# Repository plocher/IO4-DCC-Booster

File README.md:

# IO4-DCC-Booster
## License: CERN Open Hardware Licence v1.2

IO4 DCC Booster

A DIY DCC booster for a BOM cost of about $20 when using bulk China/eBay parts.

I was working on designing a motor shield using the $10 IBT-2
H-Bridge when I came across the work done by D. Bodnar at
[train electronics.com](http://www.trainelectronics.com/DCC_Arduino/DCC_Booster/)

I wanted to use one of these for every control point on my layout
instead of a DCC circuit breaker + booster power district mashup.
As the DCC Breakers are at least double the DIY cost for these
dedicated boosters, and I will end up with 10-20 control points on
my SPCoast layout, the savings might actually cover the development
costs :-)

These boosters DO NOT support auto-reverse, and the sketch software
doesn't try to do soft start detection of sound decoder capacitor
inrush currents.  Since there will be on average a single train
powered by each of these boosters on my N-Scale layout, I don't
expect this to be a real issue.  In practice, a simple 1 or 2 amp
unit would probably be good enough; at 5 to 6 amps, this is overkill.

From the original web writeup at trainelectronics.com:

<blockquote>
Introduction

In addition to experimenting with DCC++ over the last few months I
have been trying out different H-Bridges to see if there is one
that would work with DCC++ while delivering more than the 1 to 2
amps that the standard Arduino Motor Shield provides.  Such a option
would a good option for G scale layouts that typically draw much
more power than smaller scales.

I came across a few higher power shields
[that are described here](http://trainelectronics.com/DCC_Arduino/DCC++/)
including one that has an advertised power capability of 43 amps.
While I am a bit skeptical about this claim my tests show that it
has no problem delivering 5 or more amps, more than enough for my
purposes.  I describe how this can be interfaced to the DCC++
controller in the link above.

In order to make the use of this H-Bridge more convenient I decided
to design a stand-alone DCC booster that would attach to a DCC
signal and boost it before powering a track.  The booster is designed
to work with DCC++, Digitrax and other systems.

Hardware - H-Bridge

The H-Bridge is available from eBay, Amazon and other vendors -
just search for "H-Bridge 43 amp BTS7960B".  Make sure you get the
unit that has two BTS7960B devices on it - each is 1/2 of an H-Bridge.
The control signals go to the 8 pins on the front and the power in
and power out wires go to the 4 pin screw terminal connector at the
rear.

This H-Bridge and similar units do not operate on the single PWM
signal that most DCC systems provide.  It needs a right hand rotating
PWM and a left hand PWM.  To change the single PWM signal to two a
simple one transistor circuit is needed.  That circuit can be seen
in the lower left corner of the schematic (below).

The H-Bridge can act as a DCC booster without much more than the
Opto Coupler circuit and the one transistor converter.  The H-Bridge
does hove an over current shutdown capability but it doesn't react
until well over 30 amps are being drawn, way more than we are going
to use.  To get around this problem so that the system shuts down
immediately if the track is shorted an Arduino Pro Mini has been
added.  The Arduino monitors the current sensing pin on the H-Bridge
and can turn it off should it detect a high reading.

</blockquote>

His prototype reused a board he had on hand; this project simply
turns his schematic into a purpose-built board - and adds remote control
(enable/disable and monitoring) via an IO-4 RJ12/6 interface.

The differences:
  * powered by (3.0) the IO-4 Jack / IOexpander and (3.1) by the DC booster power.
  * local control - a maintainer "disable track power" switch
  * remote control
    * enable/disable track power
  * remote feedback
    * enabled
    * occupied
    * overload
  * Loconet and NCE Booster Bus daisy chain command station cable jacks

=== Estimated BOM costs ===
:	$ 1.00  PCB 
:	$10.00  IBT-2 
:	$ 3.50  Pro Mini Clone
:	$ 0.45  6n137
:	$ 0.20  2200uF x2
:	$ 3.00  RJ and Phoenix connectors
:	$ 1.00  SPDT Switch
:	$ 1.00  R/C/LEDs
:	------
:      ~$20.00

The booster will also need a 12-18v 6A+ DC power supply; the logic and
feedback electronics are isolated from the power supply (using opto
isolator for the booster bus and a full wave bridge for the power
supply), so there should be no problems driving a set of boosters
from a single large amperage switching supply.

As with ALL high power systems, use a SLOW BLOW or POLYFUSE in your
power supply feed.  20v at 6A is 120W - similar to a very bright
and hot incandescent bulb, if you remember them.  You don't want
to arc weld or start a fire on your layout if something goes wrong!

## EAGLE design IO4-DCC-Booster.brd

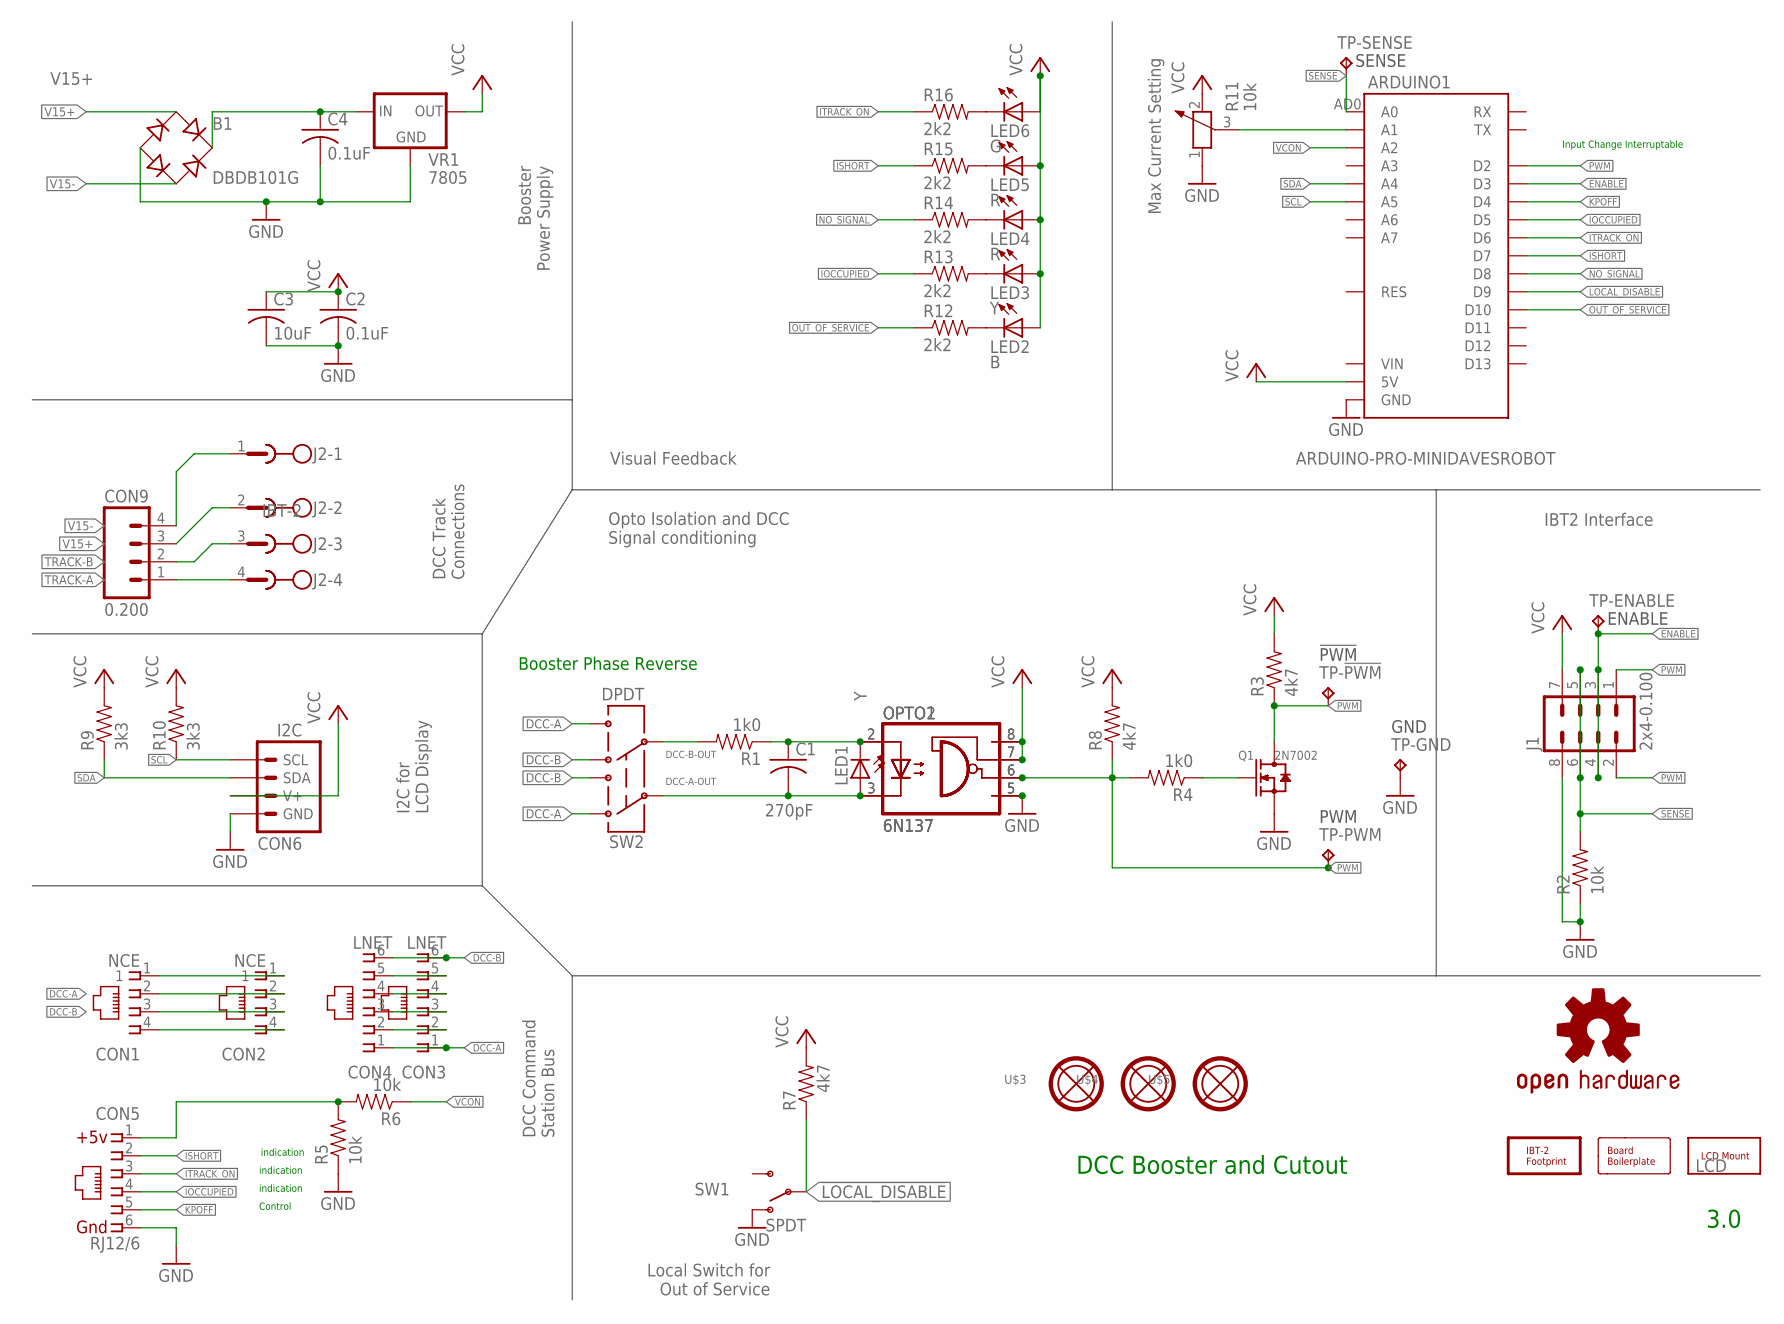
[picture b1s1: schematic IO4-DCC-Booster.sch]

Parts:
ARDUINO1: ARDUINO-PRO-MINIDAVESROBOT; ARDUINO_PRO_MINI_DAVEK
B1: DBDB101G; DB
BOARD1: BOARD100X100-NOHOLES; BOARD-SEEED10X10-NOHOLES
C1: 270pF; 0805-CAP
C2, C4: 0.1uF; 0805-CAP
C3: 10uF; 0805-CAP
CON1, CON2: NCE; 555980-1
CON3, CON4: LNET; RJ25-PANEL
CON5: RJ12/6; RJ25-PANEL
CON6: I2C; I2C-L
CON9: 0.200; MSTBA4
J1: 2x4-0.100; MA04-2
J2: IBT-2; MSTBA4
LCD: LCD; LCD-16X2-SILK
LED1, LED3: Y; 0603-LED
LED2: B; 0603-LED
LED4, LED5: R; 0603-LED
LED6: G; 0603-LED
LOGO1: DOC-OSHW-LOGO-L; OSHW-LOGO-L
OPTO1: 6N137; DIL08
OPTO2: 6N137; SM8
Q1: 2N7002; SOT23
R1, R4: 1k0; 0805-RES
R2, R5, R6: 10k; 0805-RES
R3, R7, R8: 4k7; 0805-RES
R9, R10: 3k3; 0805-RES
R11: 10k; B25X
R12, R13, R14, R15, R16: 2k2; 0805-RES
SW1: SPDT; SWITCH-SPDT-508
SW2: DPDT; 8X8-SQ-PB
TP-!PWM: TPPAD1-13; P1-13
TP-ENABLE: TPPAD1-13; P1-13
TP-GND: TPPAD1-13; P1-13
TP-PWM: TPPAD1-13; P1-13
TP-SENSE: TPPAD1-13; P1-13
U$2: IBT-2
U$3, U$4, U$5: MOUNTINGHOLE
VR1: 7805; TO-252

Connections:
!IOCCUPIED: ARDUINO1.D5, CON5.4, R13.1
!ISHORT: ARDUINO1.D7, CON5.2, R15.1
!ITRACK_ON: ARDUINO1.D6, CON5.3, R16.1
!KPOFF: ARDUINO1.D4, CON5.5
!LOCAL_DISABLE: ARDUINO1.D9, R7.1, SW1.2
!NO_SIGNAL: ARDUINO1.D8, R14.1
!OUT_OF_SERVICE: ARDUINO1.D10, R12.1
!PWM: J1.2, Q1.3 (D), R3.1, TP-!PWM.TP
DCC-A: CON1.2, CON2.2, CON3.1, CON4.1, SW2.1A, SW2.2B
DCC-A-OUT: C1.2, LED1.A, OPTO1.3 (C), OPTO2.3 (C), SW2.1C
DCC-B: CON1.3, CON2.3, CON3.6, CON4.6, SW2.1B, SW2.2A
DCC-B-LIMITED: C1.1, LED1.C, OPTO1.2 (A), OPTO2.2 (A), R1.1
DCC-B-OUT: R1.2, SW2.2C
ENABLE: ARDUINO1.D3, J1.3, J1.4, TP-ENABLE.TP
GND: ARDUINO1.GND@1 (GND), ARDUINO1.GND@2 (GND), ARDUINO1.GND@4 (GND), B1.-, C2.2, C3.2, C4.2, CON5.6, CON6.GND, CON6.GND@1 (GND), J1.8, OPTO1.5 (GND), OPTO2.5 (GND), Q1.2 (S), R2.1, R5.1, R11.1, SW1.1 (O), TP-GND.TP, VR1.2 (GND)
LIMIT: ARDUINO1.AD1 (A1), R11.3 (2)
unnamed: Q1.1 (G), R4.1
unnamed: CON1.4, CON2.4
unnamed: CON1.1, CON2.1
unnamed: CON3.5, CON4.5
unnamed: CON3.4, CON4.4
unnamed: LED4.C, R14.2
unnamed: CON3.3, CON4.3
unnamed: LED2.C, R12.2
unnamed: LED3.C, R13.2
unnamed: LED6.C, R16.2
unnamed: LED5.C, R15.2
unnamed: CON3.2, CON4.2
unnamed: B1.+, C4.1, VR1.1 (IN)
PWM: ARDUINO1.D2, J1.1, OPTO1.6 (VO), OPTO2.6 (VO), R4.2, R8.1, TP-PWM.TP
SCL: ARDUINO1.AD5 (A5), CON6.SCL, CON6.SCL@1 (SCL), R10.1
SDA: ARDUINO1.AD4 (A4), CON6.SDA, CON6.SDA@1 (SDA), R9.1
SENSE: ARDUINO1.AD0 (A0), J1.5, J1.6, R2.2, TP-SENSE.TP
TRACK-A: CON9.1, J2.4
TRACK-B: CON9.2, J2.3
V15+: B1.AC1, CON9.3, J2.2
V15-: B1.AC2, CON9.4, J2.1
VCC: ARDUINO1.5V, C2.1, C3.1, CON6.V+, CON6.V+@1 (V+), J1.7, LED2.A, LED3.A, LED4.A, LED5.A, LED6.A, OPTO1.7 (VE), OPTO1.8 (VCC), OPTO2.7 (VE), OPTO2.8 (VCC), R3.2, R7.2, R8.2, R9.2, R10.2, R11.2 (3), VR1.3 (OUT)
VCOMPUTER: CON5.1, R5.2, R6.2
VCON: ARDUINO1.AD2 (A2), R6.1

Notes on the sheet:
3.0
DCC Booster and Cutout
Control
indication
Input Change Interruptable
Max Current Setting
Visual Feedback
Booster Power Supply
DCC Track Connections
I2C for LCD Display
DCC Command Station Bus
Local Switch for Out of Service
Opto Isolation and DCC Signal conditioning
IBT2 Interface
Booster Phase Reverse

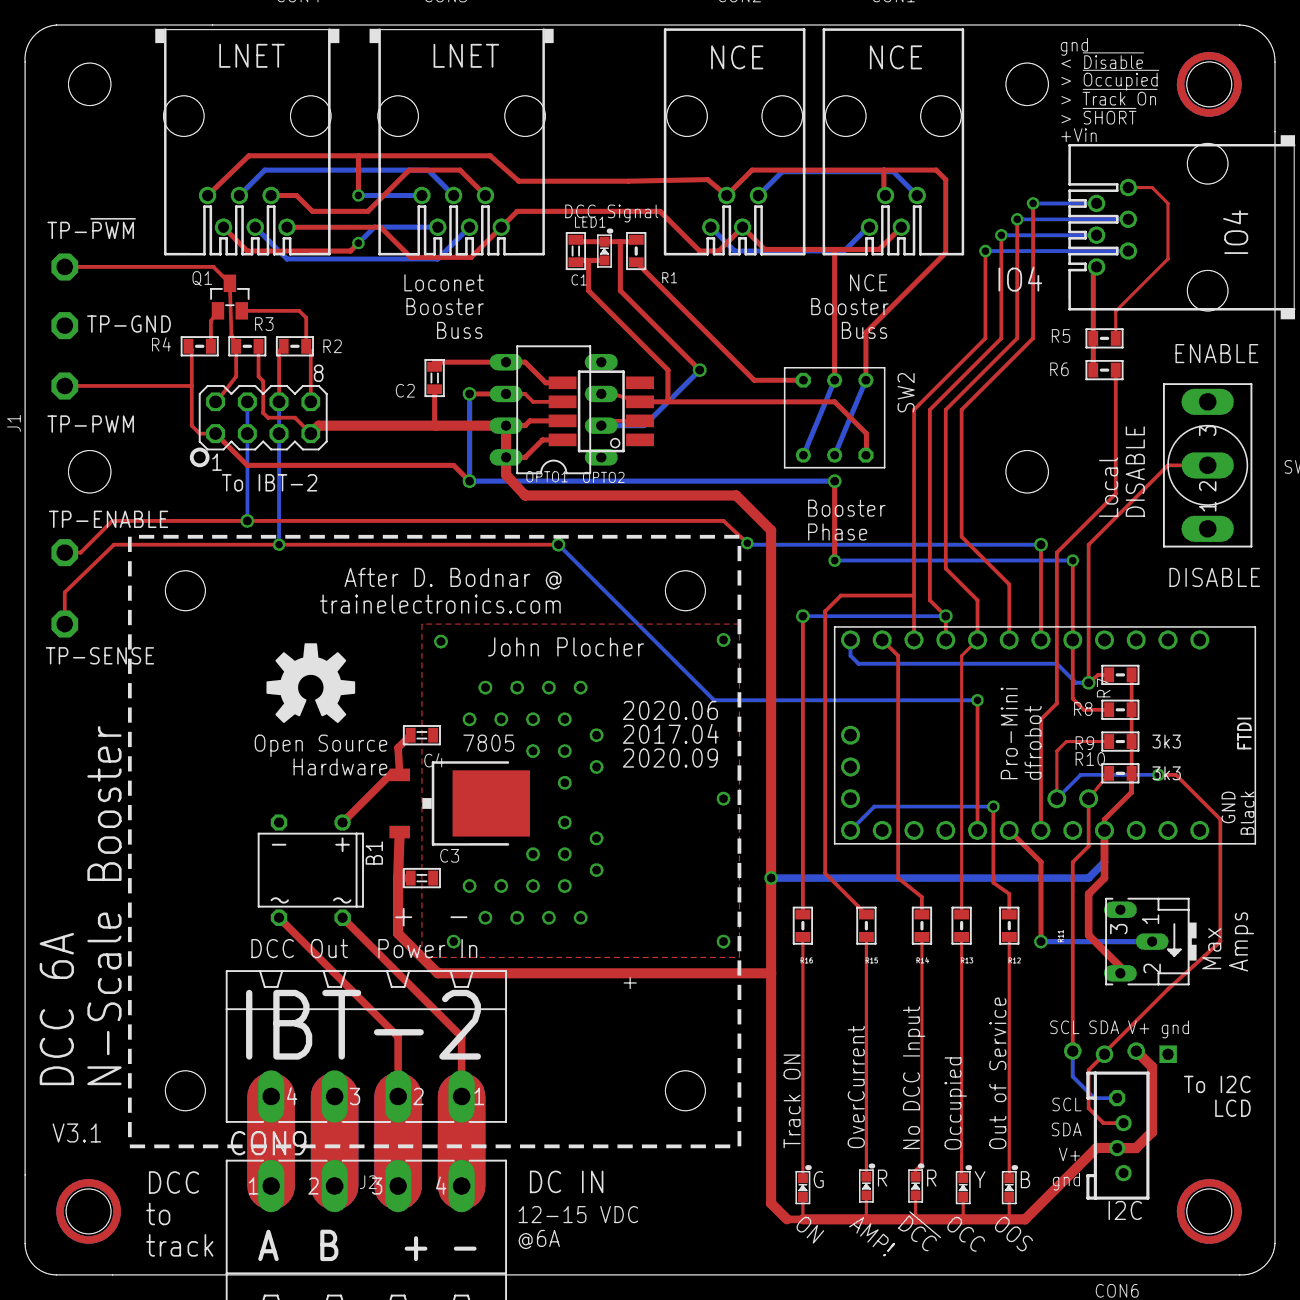
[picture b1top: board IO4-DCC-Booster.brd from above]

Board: 2 copper layers, 100.0 x 100.0 mm, 55 parts (0 on the bottom side), 40 nets.

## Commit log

2020-09-29 Initial version
2020-09-29 Rework, DC supply, simpler trace layout
2020-09-29 cleanup
2020-10-06 normalized values

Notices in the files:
parts and their libraries:
SPCoast: http://freedomdefined.org/OSHW Creative Commons - Attribution - ShareAlike 3.0
